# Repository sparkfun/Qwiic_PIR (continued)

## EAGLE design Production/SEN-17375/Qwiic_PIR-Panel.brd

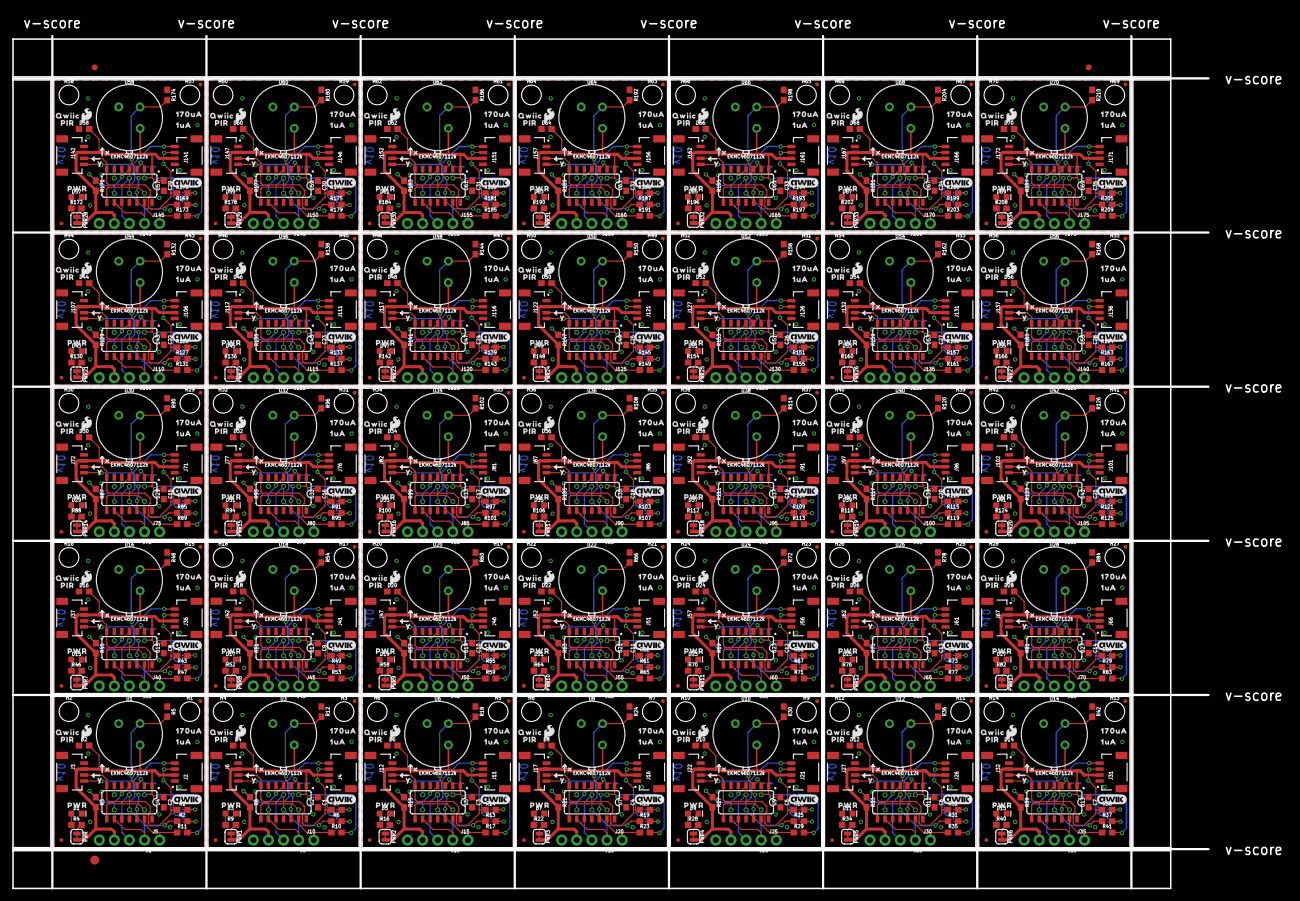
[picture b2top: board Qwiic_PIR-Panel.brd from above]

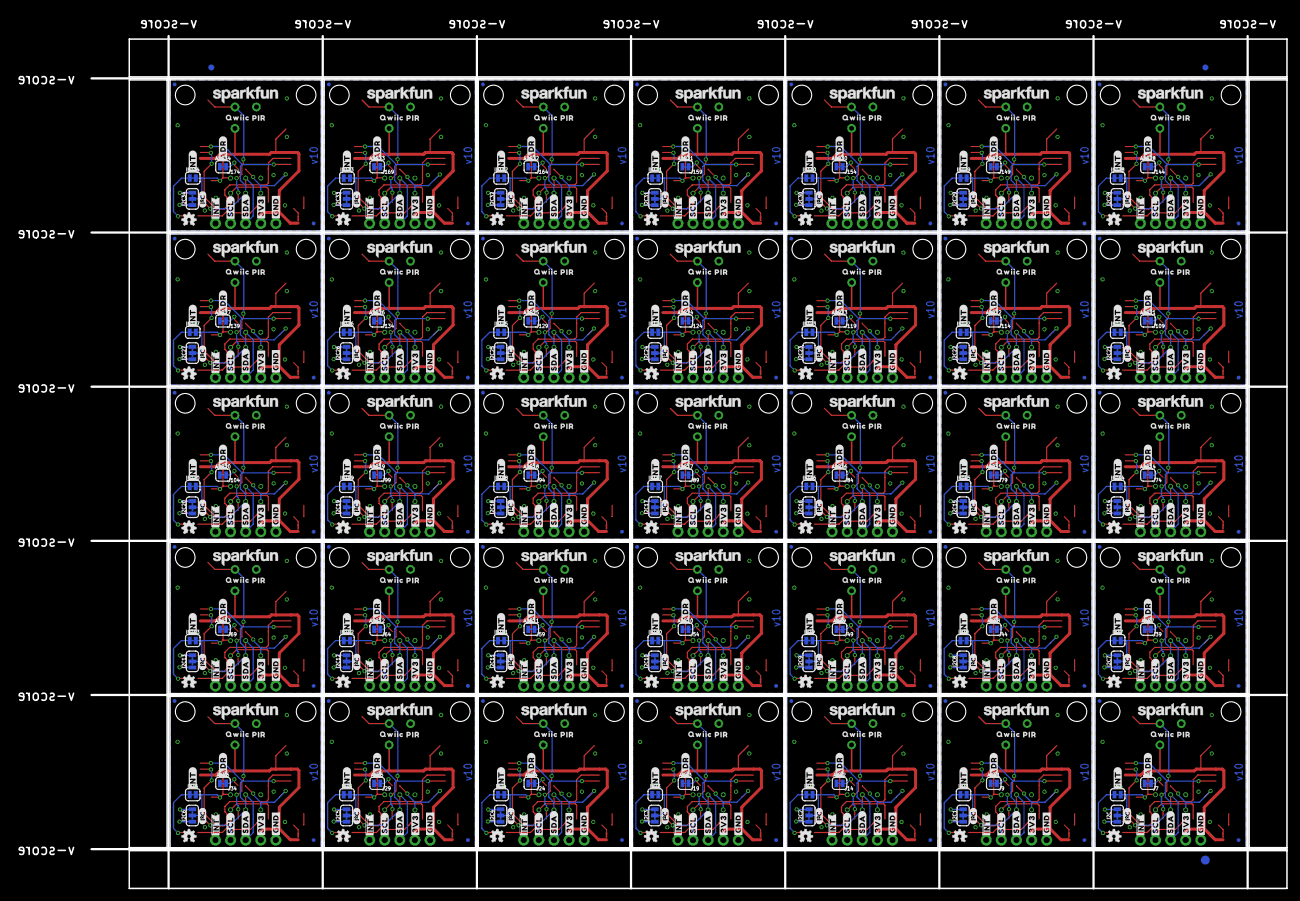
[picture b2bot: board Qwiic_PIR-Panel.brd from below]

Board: 2 copper layers, 214.1 x 147.1 mm, 1651 parts (633 on the bottom side), 490 nets.

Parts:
ADR, ADR1, ADR2, ADR3, ADR4, ADR5, ADR6, ADR7, ADR8, ADR9, ADR10, ADR11, ADR12, ADR13, ADR14, ADR15, ADR16, ADR17, ADR18, ADR19, ADR20, ADR21, ADR22, ADR23, ADR24, ADR25, ADR26, ADR27, ADR28, ADR29, ADR30, ADR31, ADR32, ADR33, ADR34: JUMPER-SMT_2_NC_TRACE_SILK; SMT-JUMPER_2_NC_TRACE_SILK
C1, C2, C3, C4, C5, C6, C7, C8, C9, C10, C11, C12, C13, C14, C15, C16, C17, C18, C19, C20, C21, C22, C23, C24, C25, C26, C27, C28, C29, C30, C31, C32, C33, C34, C35: 0.1uF; 0603
D1, D3, D5, D7, D9, D11, D13, D15, D17, D19, D21, D23, D25, D27, D29, D31, D33, D35, D37, D39, D41, D43, D45, D47, D49, D51, D53, D55, D57, D59, D61, D63, D65, D67, D69: RED; LED-0603
D2, D4, D6, D8, D10, D12, D14, D16, D18, D20, D22, D24, D26, D28, D30, D32, D34, D36, D38, D40, D42, D44, D46, D48, D50, D52, D54, D56, D58, D60, D62, D64, D66, D68, D70: 24V; 0603
E$1, E$2, E$3, E$4: FIDUCIAL-1X2
E$5, E$6: FIDUCIAL-1.5X3
H1, H2, H3, H4, H5, H6, H7, H8, H9, H10, H11, H12, H13, H14, H15, H16, H17, H18, H19, H20, H21, H22, H23, H24, H25, H26, H27, H28, H29, H30, H31, H32, H33, H34, H35, H36, H37, H38, H39, H40, H41, H42, H43, H44, H45, H46, H47, H48, H49, H50, H51, H52, H53, H54, H55, H56, H57, H58, H59, H60, H61, H62, H63, H64, H65, H66, H67, H68, H69, H70: STAND-OFF
I2C, I2C1, I2C2, I2C3, I2C4, I2C5, I2C6, I2C7, I2C8, I2C9, I2C10, I2C11, I2C12, I2C13, I2C14, I2C15, I2C16, I2C17, I2C18, I2C19, I2C20, I2C21, I2C22, I2C23, I2C24, I2C25, I2C26, I2C27, I2C28, I2C29, I2C30, I2C31, I2C32, I2C33, I2C34: JUMPER-SMT_3_2-NC_TRACE_SILK; SMT-JUMPER_3_2-NC_TRACE_SILK
INT, INT1, INT2, INT3, INT4, INT5, INT6, INT7, INT8, INT9, INT10, INT11, INT12, INT13, INT14, INT15, INT16, INT17, INT18, INT19, INT20, INT21, INT22, INT23, INT24, INT25, INT26, INT27, INT28, INT29, INT30, INT31, INT32, INT33, INT34: JUMPER-SMT_2_NC_TRACE_SILK; SMT-JUMPER_2_NC_TRACE_SILK
J1, J8, J13, J18, J23, J28, J33, J38, J43, J48, J53, J58, J63, J68, J73, J78, J83, J88, J93, J98, J103, J108, J113, J118, J123, J128, J133, J138, J143, J148, J153, J158, J163, J168, J173: 1X04_NO_SILK
J2, J3, J4, J6, J11, J12, J16, J17, J21, J22, J26, J27, J31, J32, J36, J37, J41, J42, J46, J47, J51, J52, J56, J57, J61, J62, J66, J67, J71, J72, J76, J77, J81, J82, J86, J87, J91, J92, J96, J97, J101, J102, J106, J107, J111, J112, J116, J117, J121, J122, J126, J127, J131, J132, J136, J137, J141, J142, J146, J147, J151, J152, J156, J157, J161, J162, J166, J167, J171, J172: QWIIC; JST04_1MM_RA
J5, J10, J15, J20, J25, J30, J35, J40, J45, J50, J55, J60, J65, J70, J75, J80, J85, J90, J95, J100, J105, J110, J115, J120, J125, J130, J135, J140, J145, J150, J155, J160, J165, J170, J175: 1X01_NO_SILK
J7, J9, J14, J19, J24, J29, J34, J39, J44, J49, J54, J59, J64, J69, J74, J79, J84, J89, J94, J99, J104, J109, J114, J119, J124, J129, J134, J139, J144, J149, J154, J159, J164, J169, J174: ISP; 2X3_TEST_POINTS
JP1, JP2, JP3, JP4, JP5, JP6, JP7, JP8, JP9, JP10, JP11, JP12, JP13, JP14, JP15, JP16, JP17, JP18, JP19, JP20, JP21, JP22, JP23, JP24, JP25, JP26, JP27, JP28, JP29, JP30, JP31, JP32, JP33, JP34, JP35, JP36, JP37, JP38, JP39, JP40, JP41, JP42, JP43, JP44, JP45, JP46, JP47, JP48, JP49, JP50, JP51, JP52, JP53, JP54, JP55, JP56, JP57, JP58, JP59, JP60, JP61, JP62, JP63, JP64, JP65, JP66, JP67, JP68, JP69, JP70, JP71, JP72, JP73, JP74, JP75, JP76, JP77, JP78, JP79, JP80, JP81, JP82, JP83, JP84, JP85, JP86, JP87, JP88, JP89, JP90, JP91, JP92, JP93, JP94, JP95, JP96, JP97, JP98, JP99, JP100, JP101, JP102, JP103, JP104, JP105, JP106, JP107, JP108, JP109, JP110, JP111, JP112, JP113, JP114, JP115, JP116, JP117, JP118, JP119, JP120, JP121, JP122, JP123, JP124, JP125, JP126, JP127, JP128, JP129, JP130, JP131, JP132, JP133, JP134, JP135, JP136, JP137, JP138, JP139, JP140: FIDUCIALUFIDUCIAL; MICRO-FIDUCIAL
LOGO1, LOGO5, LOGO9, LOGO13, LOGO17, LOGO21, LOGO25, LOGO29, LOGO33, LOGO37, LOGO41, LOGO45, LOGO49, LOGO53, LOGO57, LOGO61, LOGO65, LOGO69, LOGO73, LOGO77, LOGO81, LOGO85, LOGO89, LOGO93, LOGO97, LOGO101, LOGO105, LOGO109, LOGO113, LOGO117, LOGO121, LOGO125, LOGO129, LOGO133, LOGO137: OSHW-LOGOMINI; OSHW-LOGO-MINI
LOGO2, LOGO8, LOGO12, LOGO16, LOGO20, LOGO24, LOGO28, LOGO32, LOGO36, LOGO40, LOGO44, LOGO48, LOGO52, LOGO56, LOGO60, LOGO64, LOGO68, LOGO72, LOGO76, LOGO80, LOGO84, LOGO88, LOGO92, LOGO96, LOGO100, LOGO104, LOGO108, LOGO112, LOGO116, LOGO120, LOGO124, LOGO128, LOGO132, LOGO136, LOGO140: QWIIC_LOGO_5MM; QWIIC_5MM
LOGO3, LOGO6, LOGO10, LOGO14, LOGO18, LOGO22, LOGO26, LOGO30, LOGO34, LOGO38, LOGO42, LOGO46, LOGO50, LOGO54, LOGO58, LOGO62, LOGO66, LOGO70, LOGO74, LOGO78, LOGO82, LOGO86, LOGO90, LOGO94, LOGO98, LOGO102, LOGO106, LOGO110, LOGO114, LOGO118, LOGO122, LOGO126, LOGO130, LOGO134, LOGO138: SFE_LOGO_NAME.1_INCH; SFE_LOGO_NAME_.1
LOGO4, LOGO7, LOGO11, LOGO15, LOGO19, LOGO23, LOGO27, LOGO31, LOGO35, LOGO39, LOGO43, LOGO47, LOGO51, LOGO55, LOGO59, LOGO63, LOGO67, LOGO71, LOGO75, LOGO79, LOGO83, LOGO87, LOGO91, LOGO95, LOGO99, LOGO103, LOGO107, LOGO111, LOGO115, LOGO119, LOGO123, LOGO127, LOGO131, LOGO135, LOGO139: SFE_LOGO_FLAME.1_INCH; SFE_LOGO_FLAME_.1
PWR, PWR1, PWR2, PWR3, PWR4, PWR5, PWR6, PWR7, PWR8, PWR9, PWR10, PWR11, PWR12, PWR13, PWR14, PWR15, PWR16, PWR17, PWR18, PWR19, PWR20, PWR21, PWR22, PWR23, PWR24, PWR25, PWR26, PWR27, PWR28, PWR29, PWR30, PWR31, PWR32, PWR33, PWR34: JUMPER-SMT_2_NC_TRACE_SILK; SMT-JUMPER_2_NC_TRACE_SILK
R1, R2, R6, R7, R13, R14, R19, R20, R25, R26, R31, R32, R37, R38, R43, R44, R49, R50, R55, R56, R61, R62, R67, R68, R73, R74, R79, R80, R85, R86, R91, R92, R97, R98, R103, R104, R109, R110, R115, R116, R121, R122, R127, R128, R133, R134, R139, R140, R145, R146, R151, R152, R157, R158, R163, R164, R169, R170, R175, R176, R181, R182, R187, R188, R193, R194, R199, R200, R205, R206: 2.2k; 0603
R3, R8, R10, R11, R15, R17, R21, R23, R27, R29, R33, R35, R39, R41, R45, R47, R51, R53, R57, R59, R63, R65, R69, R71, R75, R77, R81, R83, R87, R89, R93, R95, R99, R101, R105, R107, R111, R113, R117, R119, R123, R125, R129, R131, R135, R137, R141, R143, R147, R149, R153, R155, R159, R161, R165, R167, R171, R173, R177, R179, R183, R185, R189, R191, R195, R197, R201, R203, R207, R209: 10k; 0603
R4, R9, R16, R22, R28, R34, R40, R46, R52, R58, R64, R70, R76, R82, R88, R94, R100, R106, R112, R118, R124, R130, R136, R142, R148, R154, R160, R166, R172, R178, R184, R190, R196, R202, R208: 1k; 0603
R5, R12, R18, R24, R30, R36, R42, R48, R54, R60, R66, R72, R78, R84, R90, R96, R102, R108, R114, R120, R126, R132, R138, R144, R150, R156, R162, R168, R174, R180, R186, R192, R198, R204, R210: 47k; 0603
U1, U3, U6, U8, U10, U12, U14, U16, U18, U20, U22, U24, U26, U28, U30, U32, U34, U36, U38, U40, U42, U44, U46, U48, U50, U52, U54, U56, U58, U60, U62, U64, U66, U68, U70: EKMC4607112k; TO-3
U2, U4, U5, U7, U9, U11, U13, U15, U17, U19, U21, U23, U25, U27, U29, U31, U33, U35, U37, U39, U41, U43, U45, U47, U49, U51, U53, U55, U57, U59, U61, U63, U65, U67, U69: ATTINY84-ARDUINO; SO14
U$1, U$13, U$15, U$23, U$36, U$40, U$53, U$57, U$70, U$74, U$87, U$91, U$104, U$108, U$121, U$125, U$138, U$142, U$155, U$159, U$172, U$176, U$189, U$193, U$206, U$210, U$223, U$227, U$240, U$244, U$257, U$261, U$274, U$278, U$291, U$295, U$308, U$312, U$325, U$329, U$342, U$346, U$359, U$363, U$376, U$380, U$393, U$397, U$410, U$414, U$427, U$431, U$444, U$448, U$461, U$465, U$478, U$482, U$495, U$499, U$512, U$516, U$529, U$533, U$546, U$550, U$563, U$567, U$580, U$584: PIR0
U$2, U$24, U$41, U$58, U$75, U$92, U$109, U$126, U$143, U$160, U$177, U$194, U$211, U$228, U$245, U$262, U$279, U$296, U$313, U$330, U$347, U$364, U$381, U$398, U$415, U$432, U$449, U$466, U$483, U$500, U$517, U$534, U$551, U$568, U$585: 170UA0
U$3, U$20, U$37, U$54, U$71, U$88, U$105, U$122, U$139, U$156, U$173, U$190, U$207, U$224, U$241, U$258, U$275, U$292, U$309, U$326, U$343, U$360, U$377, U$394, U$411, U$428, U$445, U$462, U$479, U$496, U$513, U$530, U$547, U$564, U$581: PWR0
U$4, U$21, U$38, U$55, U$72, U$89, U$106, U$123, U$140, U$157, U$174, U$191, U$208, U$225, U$242, U$259, U$276, U$293, U$310, U$327, U$344, U$361, U$378, U$395, U$412, U$429, U$446, U$463, U$480, U$497, U$514, U$531, U$548, U$565, U$582: #INT#0
U$5, U$31, U$48, U$65, U$82, U$99, U$116, U$133, U$150, U$167, U$184, U$201, U$218, U$235, U$252, U$269, U$286, U$303, U$320, U$337, U$354, U$371, U$388, U$405, U$422, U$439, U$456, U$473, U$490, U$507, U$524, U$541, U$558, U$575, U$592: #3V3#0
U$6, U$32, U$49, U$66, U$83, U$100, U$117, U$134, U$151, U$168, U$185, U$202, U$219, U$236, U$253, U$270, U$287, U$304, U$321, U$338, U$355, U$372, U$389, U$406, U$423, U$440, U$457, U$474, U$491, U$508, U$525, U$542, U$559, U$576, U$593: #SDA#0
U$7, U$33, U$50, U$67, U$84, U$101, U$118, U$135, U$152, U$169, U$186, U$203, U$220, U$237, U$254, U$271, U$288, U$305, U$322, U$339, U$356, U$373, U$390, U$407, U$424, U$441, U$458, U$475, U$492, U$509, U$526, U$543, U$560, U$577, U$594: #SCL#0
U$8, U$34, U$51, U$68, U$85, U$102, U$119, U$136, U$153, U$170, U$187, U$204, U$221, U$238, U$255, U$272, U$289, U$306, U$323, U$340, U$357, U$374, U$391, U$408, U$425, U$442, U$459, U$476, U$493, U$510, U$527, U$544, U$561, U$578, U$595: ##INT##0
U$9, U$25, U$42, U$59, U$76, U$93, U$110, U$127, U$144, U$161, U$178, U$195, U$212, U$229, U$246, U$263, U$280, U$297, U$314, U$331, U$348, U$365, U$382, U$399, U$416, U$433, U$450, U$467, U$484, U$501, U$518, U$535, U$552, U$569, U$586: 1UA0
U$10, U$12, U$35, U$52, U$69, U$86, U$103, U$120, U$137, U$154, U$171, U$188, U$205, U$222, U$239, U$256, U$273, U$290, U$307, U$324, U$341, U$358, U$375, U$392, U$409, U$426, U$443, U$460, U$477, U$494, U$511, U$528, U$545, U$562, U$579: I_SUPER2_C-()-03
U$11, U$22, U$39, U$56, U$73, U$90, U$107, U$124, U$141, U$158, U$175, U$192, U$209, U$226, U$243, U$260, U$277, U$294, U$311, U$328, U$345, U$362, U$379, U$396, U$413, U$430, U$447, U$464, U$481, U$498, U$515, U$532, U$549, U$566, U$583: #ADR#0
U$14, U$26, U$43, U$60, U$77, U$94, U$111, U$128, U$145, U$162, U$179, U$196, U$213, U$230, U$247, U$264, U$281, U$298, U$315, U$332, U$349, U$366, U$383, U$400, U$417, U$434, U$451, U$468, U$485, U$502, U$519, U$536, U$553, U$570, U$587: X0
U$16, U$27, U$44, U$61, U$78, U$95, U$112, U$129, U$146, U$163, U$180, U$197, U$214, U$231, U$248, U$265, U$282, U$299, U$316, U$333, U$350, U$367, U$384, U$401, U$418, U$435, U$452, U$469, U$486, U$503, U$520, U$537, U$554, U$571, U$588: Y0
U$17, U$18, U$28, U$29, U$45, U$46, U$62, U$63, U$79, U$80, U$96, U$97, U$113, U$114, U$130, U$131, U$147, U$148, U$164, U$165, U$181, U$182, U$198, U$199, U$215, U$216, U$232, U$233, U$249, U$250, U$266, U$267, U$283, U$284, U$300, U$301, U$317, U$318, U$334, U$335, U$351, U$352, U$368, U$369, U$385, U$386, U$402, U$403, U$419, U$420, U$436, U$437, U$453, U$454, U$470, U$471, U$487, U$488, U$504, U$505, U$521, U$522, U$538, U$539, U$555, U$556, U$572, U$573, U$589, U$590: QWIIC0
U$19, U$30, U$47, U$64, U$81, U$98, U$115, U$132, U$149, U$166, U$183, U$200, U$217, U$234, U$251, U$268, U$285, U$302, U$319, U$336, U$353, U$370, U$387, U$404, U$421, U$438, U$455, U$472, U$489, U$506, U$523, U$540, U$557, U$574, U$591: #GND#0

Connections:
3.3V: C2.1, D2.2, I2C.2, INT.2, J1.3, J2.2, J3.2, J7.2, PWR.2, R3.2, U1.VDD, U4.1
3.3V1: C1.1, D4.2, I2C1.2, INT1.2, J4.2, J6.2, J8.3, J9.2, PWR1.2, R8.2, U2.1, U3.VDD
3.3V2: C3.1, D6.2, I2C2.2, INT2.2, J11.2, J12.2, J13.3, J14.2, PWR2.2, R15.2, U5.1, U6.VDD
3.3V3: C4.1, D8.2, I2C3.2, INT3.2, J16.2, J17.2, J18.3, J19.2, PWR3.2, R21.2, U7.1, U8.VDD
3.3V4: C5.1, D10.2, I2C4.2, INT4.2, J21.2, J22.2, J23.3, J24.2, PWR4.2, R27.2, U9.1, U10.VDD
3.3V5: C6.1, D12.2, I2C5.2, INT5.2, J26.2, J27.2, J28.3, J29.2, PWR5.2, R33.2, U11.1, U12.VDD
3.3V6: C7.1, D14.2, I2C6.2, INT6.2, J31.2, J32.2, J33.3, J34.2, PWR6.2, R39.2, U13.1, U14.VDD
3.3V7: C8.1, D16.2, I2C7.2, INT7.2, J36.2, J37.2, J38.3, J39.2, PWR7.2, R45.2, U15.1, U16.VDD
3.3V8: C9.1, D18.2, I2C8.2, INT8.2, J41.2, J42.2, J43.3, J44.2, PWR8.2, R51.2, U17.1, U18.VDD
3.3V9: C10.1, D20.2, I2C9.2, INT9.2, J46.2, J47.2, J48.3, J49.2, PWR9.2, R57.2, U19.1, U20.VDD
3.3V10: C11.1, D22.2, I2C10.2, INT10.2, J51.2, J52.2, J53.3, J54.2, PWR10.2, R63.2, U21.1, U22.VDD
3.3V11: C12.1, D24.2, I2C11.2, INT11.2, J56.2, J57.2, J58.3, J59.2, PWR11.2, R69.2, U23.1, U24.VDD
3.3V12: C13.1, D26.2, I2C12.2, INT12.2, J61.2, J62.2, J63.3, J64.2, PWR12.2, R75.2, U25.1, U26.VDD
3.3V13: C14.1, D28.2, I2C13.2, INT13.2, J66.2, J67.2, J68.3, J69.2, PWR13.2, R81.2, U27.1, U28.VDD
3.3V14: C15.1, D30.2, I2C14.2, INT14.2, J71.2, J72.2, J73.3, J74.2, PWR14.2, R87.2, U29.1, U30.VDD
3.3V15: C16.1, D32.2, I2C15.2, INT15.2, J76.2, J77.2, J78.3, J79.2, PWR15.2, R93.2, U31.1, U32.VDD
3.3V16: C17.1, D34.2, I2C16.2, INT16.2, J81.2, J82.2, J83.3, J84.2, PWR16.2, R99.2, U33.1, U34.VDD
3.3V17: C18.1, D36.2, I2C17.2, INT17.2, J86.2, J87.2, J88.3, J89.2, PWR17.2, R105.2, U35.1, U36.VDD
3.3V18: C19.1, D38.2, I2C18.2, INT18.2, J91.2, J92.2, J93.3, J94.2, PWR18.2, R111.2, U37.1, U38.VDD
3.3V19: C20.1, D40.2, I2C19.2, INT19.2, J96.2, J97.2, J98.3, J99.2, PWR19.2, R117.2, U39.1, U40.VDD
3.3V20: C21.1, D42.2, I2C20.2, INT20.2, J101.2, J102.2, J103.3, J104.2, PWR20.2, R123.2, U41.1, U42.VDD
3.3V21: C22.1, D44.2, I2C21.2, INT21.2, J106.2, J107.2, J108.3, J109.2, PWR21.2, R129.2, U43.1, U44.VDD
3.3V22: C23.1, D46.2, I2C22.2, INT22.2, J111.2, J112.2, J113.3, J114.2, PWR22.2, R135.2, U45.1, U46.VDD
3.3V23: C24.1, D48.2, I2C23.2, INT23.2, J116.2, J117.2, J118.3, J119.2, PWR23.2, R141.2, U47.1, U48.VDD
3.3V24: C25.1, D50.2, I2C24.2, INT24.2, J121.2, J122.2, J123.3, J124.2, PWR24.2, R147.2, U49.1, U50.VDD
3.3V25: C26.1, D52.2, I2C25.2, INT25.2, J126.2, J127.2, J128.3, J129.2, PWR25.2, R153.2, U51.1, U52.VDD
3.3V26: C27.1, D54.2, I2C26.2, INT26.2, J131.2, J132.2, J133.3, J134.2, PWR26.2, R159.2, U53.1, U54.VDD
3.3V27: C28.1, D56.2, I2C27.2, INT27.2, J136.2, J137.2, J138.3, J139.2, PWR27.2, R165.2, U55.1, U56.VDD
3.3V28: C29.1, D58.2, I2C28.2, INT28.2, J141.2, J142.2, J143.3, J144.2, PWR28.2, R171.2, U57.1, U58.VDD
3.3V29: C30.1, D60.2, I2C29.2, INT29.2, J146.2, J147.2, J148.3, J149.2, PWR29.2, R177.2, U59.1, U60.VDD
3.3V30: C31.1, D62.2, I2C30.2, INT30.2, J151.2, J152.2, J153.3, J154.2, PWR30.2, R183.2, U61.1, U62.VDD
3.3V31: C32.1, D64.2, I2C31.2, INT31.2, J156.2, J157.2, J158.3, J159.2, PWR31.2, R189.2, U63.1, U64.VDD
3.3V32: C33.1, D66.2, I2C32.2, INT32.2, J161.2, J162.2, J163.3, J164.2, PWR32.2, R195.2, U65.1, U66.VDD
3.3V33: C34.1, D68.2, I2C33.2, INT33.2, J166.2, J167.2, J168.3, J169.2, PWR33.2, R201.2, U67.1, U68.VDD
3.3V34: C35.1, D70.2, I2C34.2, INT34.2, J171.2, J172.2, J173.3, J174.2, PWR34.2, R207.2, U69.1, U70.VDD
!INT: J5.1, R11.1, U4.13
!INT1: J10.1, R10.1, U2.13
!INT2: J15.1, R17.1, U5.13
!INT3: J20.1, R23.1, U7.13
!INT4: J25.1, R29.1, U9.13
!INT5: J30.1, R35.1, U11.13
!INT6: J35.1, R41.1, U13.13
!INT7: J40.1, R47.1, U15.13
!INT8: J45.1, R53.1, U17.13
!INT9: J50.1, R59.1, U19.13
!INT10: J55.1, R65.1, U21.13
!INT11: J60.1, R71.1, U23.13
!INT12: J65.1, R77.1, U25.13
!INT13: J70.1, R83.1, U27.13
!INT14: J75.1, R89.1, U29.13
!INT15: J80.1, R95.1, U31.13
!INT16: J85.1, R101.1, U33.13
!INT17: J90.1, R107.1, U35.13
!INT18: J95.1, R113.1, U37.13
!INT19: J100.1, R119.1, U39.13
!INT20: J105.1, R125.1, U41.13
!INT21: J110.1, R131.1, U43.13
!INT22: J115.1, R137.1, U45.13
!INT23: J120.1, R143.1, U47.13
!INT24: J125.1, R149.1, U49.13
!INT25: J130.1, R155.1, U51.13
!INT26: J135.1, R161.1, U53.13
!INT27: J140.1, R167.1, U55.13
!INT28: J145.1, R173.1, U57.13
!INT29: J150.1, R179.1, U59.13
!INT30: J155.1, R185.1, U61.13
!INT31: J160.1, R191.1, U63.13
!INT32: J165.1, R197.1, U65.13
!INT33: J170.1, R203.1, U67.13
!INT34: J175.1, R209.1, U69.13
!RST: J7.5, R3.1, U4.4
!RST1: J9.5, R8.1, U2.4
!RST2: J14.5, R15.1, U5.4
!RST3: J19.5, R21.1, U7.4
!RST4: J24.5, R27.1, U9.4
!RST5: J29.5, R33.1, U11.4
!RST6: J34.5, R39.1, U13.4
!RST7: J39.5, R45.1, U15.4
!RST8: J44.5, R51.1, U17.4
!RST9: J49.5, R57.1, U19.4
!RST10: J54.5, R63.1, U21.4
!RST11: J59.5, R69.1, U23.4
!RST12: J64.5, R75.1, U25.4
!RST13: J69.5, R81.1, U27.4
!RST14: J74.5, R87.1, U29.4
!RST15: J79.5, R93.1, U31.4
!RST16: J84.5, R99.1, U33.4
!RST17: J89.5, R105.1, U35.4
!RST18: J94.5, R111.1, U37.4
!RST19: J99.5, R117.1, U39.4
!RST20: J104.5, R123.1, U41.4
!RST21: J109.5, R129.1, U43.4
!RST22: J114.5, R135.1, U45.4
!RST23: J119.5, R141.1, U47.4
!RST24: J124.5, R147.1, U49.4
!RST25: J129.5, R153.1, U51.4
!RST26: J134.5, R159.1, U53.4
!RST27: J139.5, R165.1, U55.4
!RST28: J144.5, R171.1, U57.4
!RST29: J149.5, R177.1, U59.4
!RST30: J154.5, R183.1, U61.4
!RST31: J159.5, R189.1, U63.4
!RST32: J164.5, R195.1, U65.4
!RST33: J169.5, R201.1, U67.4
!RST34: J174.5, R207.1, U69.4
ADR0: ADR.2, U4.3
ADR1: ADR1.2, U2.3
ADR2: ADR2.2, U5.3
ADR3: ADR3.2, U7.3
ADR4: ADR4.2, U9.3
ADR5: ADR5.2, U11.3
ADR6: ADR6.2, U13.3
ADR7: ADR7.2, U15.3
ADR8: ADR8.2, U17.3
ADR9: ADR9.2, U19.3
ADR10: ADR10.2, U21.3
ADR11: ADR11.2, U23.3
ADR12: ADR12.2, U25.3
ADR13: ADR13.2, U27.3
ADR14: ADR14.2, U29.3
ADR15: ADR15.2, U31.3
ADR16: ADR16.2, U33.3
ADR17: ADR17.2, U35.3
ADR18: ADR18.2, U37.3
ADR19: ADR19.2, U39.3
ADR20: ADR20.2, U41.3
ADR21: ADR21.2, U43.3
ADR22: ADR22.2, U45.3
ADR23: ADR23.2, U47.3
ADR24: ADR24.2, U49.3
ADR25: ADR25.2, U51.3
ADR26: ADR26.2, U53.3
ADR27: ADR27.2, U55.3
ADR28: ADR28.2, U57.3
ADR29: ADR29.2, U59.3
ADR30: ADR30.2, U61.3
ADR31: ADR31.2, U63.3
ADR32: ADR32.2, U65.3
ADR33: ADR33.2, U67.3
ADR34: ADR34.2, U69.3
GND: ADR.1, C2.2, D1.C, D2.1, J1.4, J2.1, J3.1, J7.6, R5.1, U1.GND, U4.14
GND1: ADR1.1, C1.2, D3.C, D4.1, J4.1, J6.1, J8.4, J9.6, R12.1, U2.14, U3.GND
GND2: ADR2.1, C3.2, D5.C, D6.1, J11.1, J12.1, J13.4, J14.6, R18.1, U5.14, U6.GND
GND3: ADR3.1, C4.2, D7.C, D8.1, J16.1, J17.1, J18.4, J19.6, R24.1, U7.14, U8.GND
GND4: ADR4.1, C5.2, D9.C, D10.1, J21.1, J22.1, J23.4, J24.6, R30.1, U9.14, U10.GND
GND5: ADR5.1, C6.2, D11.C, D12.1, J26.1, J27.1, J28.4, J29.6, R36.1, U11.14, U12.GND
GND6: ADR6.1, C7.2, D13.C, D14.1, J31.1, J32.1, J33.4, J34.6, R42.1, U13.14, U14.GND
GND7: ADR7.1, C8.2, D15.C, D16.1, J36.1, J37.1, J38.4, J39.6, R48.1, U15.14, U16.GND
GND8: ADR8.1, C9.2, D17.C, D18.1, J41.1, J42.1, J43.4, J44.6, R54.1, U17.14, U18.GND
GND9: ADR9.1, C10.2, D19.C, D20.1, J46.1, J47.1, J48.4, J49.6, R60.1, U19.14, U20.GND
GND10: ADR10.1, C11.2, D21.C, D22.1, J51.1, J52.1, J53.4, J54.6, R66.1, U21.14, U22.GND
GND11: ADR11.1, C12.2, D23.C, D24.1, J56.1, J57.1, J58.4, J59.6, R72.1, U23.14, U24.GND
GND12: ADR12.1, C13.2, D25.C, D26.1, J61.1, J62.1, J63.4, J64.6, R78.1, U25.14, U26.GND
GND13: ADR13.1, C14.2, D27.C, D28.1, J66.1, J67.1, J68.4, J69.6, R84.1, U27.14, U28.GND
GND14: ADR14.1, C15.2, D29.C, D30.1, J71.1, J72.1, J73.4, J74.6, R90.1, U29.14, U30.GND
GND15: ADR15.1, C16.2, D31.C, D32.1, J76.1, J77.1, J78.4, J79.6, R96.1, U31.14, U32.GND
GND16: ADR16.1, C17.2, D33.C, D34.1, J81.1, J82.1, J83.4, J84.6, R102.1, U33.14, U34.GND
GND17: ADR17.1, C18.2, D35.C, D36.1, J86.1, J87.1, J88.4, J89.6, R108.1, U35.14, U36.GND
GND18: ADR18.1, C19.2, D37.C, D38.1, J91.1, J92.1, J93.4, J94.6, R114.1, U37.14, U38.GND
GND19: ADR19.1, C20.2, D39.C, D40.1, J96.1, J97.1, J98.4, J99.6, R120.1, U39.14, U40.GND
GND20: ADR20.1, C21.2, D41.C, D42.1, J101.1, J102.1, J103.4, J104.6, R126.1, U41.14, U42.GND
GND21: ADR21.1, C22.2, D43.C, D44.1, J106.1, J107.1, J108.4, J109.6, R132.1, U43.14, U44.GND
GND22: ADR22.1, C23.2, D45.C, D46.1, J111.1, J112.1, J113.4, J114.6, R138.1, U45.14, U46.GND
GND23: ADR23.1, C24.2, D47.C, D48.1, J116.1, J117.1, J118.4, J119.6, R144.1, U47.14, U48.GND
GND24: ADR24.1, C25.2, D49.C, D50.1, J121.1, J122.1, J123.4, J124.6, R150.1, U49.14, U50.GND
GND25: ADR25.1, C26.2, D51.C, D52.1, J126.1, J127.1, J128.4, J129.6, R156.1, U51.14, U52.GND
GND26: ADR26.1, C27.2, D53.C, D54.1, J131.1, J132.1, J133.4, J134.6, R162.1, U53.14, U54.GND
GND27: ADR27.1, C28.2, D55.C, D56.1, J136.1, J137.1, J138.4, J139.6, R168.1, U55.14, U56.GND
GND28: ADR28.1, C29.2, D57.C, D58.1, J141.1, J142.1, J143.4, J144.6, R174.1, U57.14, U58.GND
GND29: ADR29.1, C30.2, D59.C, D60.1, J146.1, J147.1, J148.4, J149.6, R180.1, U59.14, U60.GND
GND30: ADR30.1, C31.2, D61.C, D62.1, J151.1, J152.1, J153.4, J154.6, R186.1, U61.14, U62.GND
GND31: ADR31.1, C32.2, D63.C, D64.1, J156.1, J157.1, J158.4, J159.6, R192.1, U63.14, U64.GND
GND32: ADR32.1, C33.2, D65.C, D66.1, J161.1, J162.1, J163.4, J164.6, R198.1, U65.14, U66.GND
GND33: ADR33.1, C34.2, D67.C, D68.1, J166.1, J167.1, J168.4, J169.6, R204.1, U67.14, U68.GND
GND34: ADR34.1, C35.2, D69.C, D70.1, J171.1, J172.1, J173.4, J174.6, R210.1, U69.14, U70.GND
INT_R: INT.1, R11.2
INT_R1: INT1.1, R10.2
INT_R2: INT2.1, R17.2
INT_R3: INT3.1, R23.2
INT_R4: INT4.1, R29.2
INT_R5: INT5.1, R35.2
INT_R6: INT6.1, R41.2
INT_R7: INT7.1, R47.2
INT_R8: INT8.1, R53.2
INT_R9: INT9.1, R59.2
INT_R10: INT10.1, R65.2
INT_R11: INT11.1, R71.2
INT_R12: INT12.1, R77.2
INT_R13: INT13.1, R83.2
INT_R14: INT14.1, R89.2
INT_R15: INT15.1, R95.2
INT_R16: INT16.1, R101.2
INT_R17: INT17.1, R107.2
INT_R18: INT18.1, R113.2
INT_R19: INT19.1, R119.2
INT_R20: INT20.1, R125.2
INT_R21: INT21.1, R131.2
INT_R22: INT22.1, R137.2
INT_R23: INT23.1, R143.2
INT_R24: INT24.1, R149.2
INT_R25: INT25.1, R155.2
INT_R26: INT26.1, R161.2
INT_R27: INT27.1, R167.2
INT_R28: INT28.1, R173.2
INT_R29: INT29.1, R179.2
INT_R30: INT30.1, R185.2
INT_R31: INT31.1, R191.2
INT_R32: INT32.1, R197.2
INT_R33: INT33.1, R203.2
INT_R34: INT34.1, R209.2
unnamed: D3.A, R9.1
unnamed: D5.A, R16.1
unnamed: D1.A, R4.1
unnamed: D7.A, R22.1
unnamed: D9.A, R28.1
unnamed: D11.A, R34.1
unnamed: D13.A, R40.1
unnamed: D15.A, R46.1
unnamed: D17.A, R52.1
unnamed: D19.A, R58.1
unnamed: D21.A, R64.1
unnamed: D23.A, R70.1
unnamed: D25.A, R76.1
unnamed: D27.A, R82.1
unnamed: D29.A, R88.1
unnamed: D31.A, R94.1
unnamed: D33.A, R100.1
unnamed: D35.A, R106.1
unnamed: D37.A, R112.1
unnamed: D39.A, R118.1
unnamed: D41.A, R124.1
unnamed: D43.A, R130.1
unnamed: D45.A, R136.1
unnamed: D47.A, R142.1
unnamed: D49.A, R148.1
unnamed: D51.A, R154.1
unnamed: D53.A, R160.1
unnamed: D55.A, R166.1
unnamed: D57.A, R172.1
unnamed: D59.A, R178.1
unnamed: D61.A, R184.1
unnamed: D63.A, R190.1
unnamed: D65.A, R196.1
unnamed: D67.A, R202.1
unnamed: D69.A, R208.1
PIR_OUT: R5.2, U1.OUT, U4.12
PIR_OUT1: R12.2, U2.12, U3.OUT
PIR_OUT2: R18.2, U5.12, U6.OUT
PIR_OUT3: R24.2, U7.12, U8.OUT
PIR_OUT4: R30.2, U9.12, U10.OUT
PIR_OUT5: R36.2, U11.12, U12.OUT
PIR_OUT6: R42.2, U13.12, U14.OUT
PIR_OUT7: R48.2, U15.12, U16.OUT
PIR_OUT8: R54.2, U17.12, U18.OUT
PIR_OUT9: R60.2, U19.12, U20.OUT
PIR_OUT10: R66.2, U21.12, U22.OUT
PIR_OUT11: R72.2, U23.12, U24.OUT
PIR_OUT12: R78.2, U25.12, U26.OUT
PIR_OUT13: R84.2, U27.12, U28.OUT
PIR_OUT14: R90.2, U29.12, U30.OUT
PIR_OUT15: R96.2, U31.12, U32.OUT
PIR_OUT16: R102.2, U33.12, U34.OUT
PIR_OUT17: R108.2, U35.12, U36.OUT
PIR_OUT18: R114.2, U37.12, U38.OUT
PIR_OUT19: R120.2, U39.12, U40.OUT
PIR_OUT20: R126.2, U41.12, U42.OUT
PIR_OUT21: R132.2, U43.12, U44.OUT
PIR_OUT22: R138.2, U45.12, U46.OUT
PIR_OUT23: R144.2, U47.12, U48.OUT
PIR_OUT24: R150.2, U49.12, U50.OUT
PIR_OUT25: R156.2, U51.12, U52.OUT
PIR_OUT26: R162.2, U53.12, U54.OUT
PIR_OUT27: R168.2, U55.12, U56.OUT
PIR_OUT28: R174.2, U57.12, U58.OUT
PIR_OUT29: R180.2, U59.12, U60.OUT
PIR_OUT30: R186.2, U61.12, U62.OUT
PIR_OUT31: R192.2, U63.12, U64.OUT
PIR_OUT32: R198.2, U65.12, U66.OUT
PIR_OUT33: R204.2, U67.12, U68.OUT
PIR_OUT34: R210.2, U69.12, U70.OUT
SCL: J1.1, J2.4, J3.4, J7.3, R2.1, U4.9
SCL1: J4.4, J6.4, J8.1, J9.3, R6.1, U2.9
SCL2: J11.4, J12.4, J13.1, J14.3, R13.1, U5.9
SCL3: J16.4, J17.4, J18.1, J19.3, R19.1, U7.9
SCL4: J21.4, J22.4, J23.1, J24.3, R25.1, U9.9
SCL5: J26.4, J27.4, J28.1, J29.3, R31.1, U11.9
SCL6: J31.4, J32.4, J33.1, J34.3, R37.1, U13.9
SCL7: J36.4, J37.4, J38.1, J39.3, R43.1, U15.9
SCL8: J41.4, J42.4, J43.1, J44.3, R49.1, U17.9
SCL9: J46.4, J47.4, J48.1, J49.3, R55.1, U19.9
SCL10: J51.4, J52.4, J53.1, J54.3, R61.1, U21.9
SCL11: J56.4, J57.4, J58.1, J59.3, R67.1, U23.9
SCL12: J61.4, J62.4, J63.1, J64.3, R73.1, U25.9
SCL13: J66.4, J67.4, J68.1, J69.3, R79.1, U27.9
SCL14: J71.4, J72.4, J73.1, J74.3, R85.1, U29.9
SCL15: J76.4, J77.4, J78.1, J79.3, R91.1, U31.9
SCL16: J81.4, J82.4, J83.1, J84.3, R97.1, U33.9
SCL17: J86.4, J87.4, J88.1, J89.3, R103.1, U35.9
SCL18: J91.4, J92.4, J93.1, J94.3, R109.1, U37.9
SCL19: J96.4, J97.4, J98.1, J99.3, R115.1, U39.9
SCL20: J101.4, J102.4, J103.1, J104.3, R121.1, U41.9
SCL21: J106.4, J107.4, J108.1, J109.3, R127.1, U43.9
SCL22: J111.4, J112.4, J113.1, J114.3, R133.1, U45.9
SCL23: J116.4, J117.4, J118.1, J119.3, R139.1, U47.9
SCL24: J121.4, J122.4, J123.1, J124.3, R145.1, U49.9
SCL25: J126.4, J127.4, J128.1, J129.3, R151.1, U51.9
SCL26: J131.4, J132.4, J133.1, J134.3, R157.1, U53.9
SCL27: J136.4, J137.4, J138.1, J139.3, R163.1, U55.9
SCL28: J141.4, J142.4, J143.1, J144.3, R169.1, U57.9
SCL29: J146.4, J147.4, J148.1, J149.3, R175.1, U59.9
SCL30: J151.4, J152.4, J153.1, J154.3, R181.1, U61.9
SCL31: J156.4, J157.4, J158.1, J159.3, R187.1, U63.9
SCL32: J161.4, J162.4, J163.1, J164.3, R193.1, U65.9
SCL33: J166.4, J167.4, J168.1, J169.3, R199.1, U67.9
SCL34: J171.4, J172.4, J173.1, J174.3, R205.1, U69.9
SCL_PU1: I2C.1, R2.2
SCL_PU2: I2C1.1, R6.2
SCL_PU3: I2C2.1, R13.2
SCL_PU4: I2C3.1, R19.2
SCL_PU5: I2C4.1, R25.2
SCL_PU6: I2C5.1, R31.2
SCL_PU7: I2C6.1, R37.2
SCL_PU8: I2C7.1, R43.2
SCL_PU9: I2C8.1, R49.2
SCL_PU10: I2C9.1, R55.2
SCL_PU11: I2C10.1, R61.2
SCL_PU12: I2C11.1, R67.2
SCL_PU13: I2C12.1, R73.2
SCL_PU14: I2C13.1, R79.2
SCL_PU15: I2C14.1, R85.2
SCL_PU16: I2C15.1, R91.2
SCL_PU17: I2C16.1, R97.2
SCL_PU18: I2C17.1, R103.2
SCL_PU19: I2C18.1, R109.2
SCL_PU20: I2C19.1, R115.2
SCL_PU21: I2C20.1, R121.2
SCL_PU22: I2C21.1, R127.2
SCL_PU23: I2C22.1, R133.2
SCL_PU24: I2C23.1, R139.2
SCL_PU25: I2C24.1, R145.2
SCL_PU26: I2C25.1, R151.2
SCL_PU27: I2C26.1, R157.2
SCL_PU28: I2C27.1, R163.2
SCL_PU29: I2C28.1, R169.2
SCL_PU30: I2C29.1, R175.2
SCL_PU31: I2C30.1, R181.2
SCL_PU32: I2C31.1, R187.2
SCL_PU33: I2C32.1, R193.2
SCL_PU34: I2C33.1, R199.2
SCL_PU35: I2C34.1, R205.2
SDA: J1.2, J2.3, J3.3, J7.4, R1.1, U4.7
SDA1: J4.3, J6.3, J8.2, J9.4, R7.1, U2.7
SDA2: J11.3, J12.3, J13.2, J14.4, R14.1, U5.7
SDA3: J16.3, J17.3, J18.2, J19.4, R20.1, U7.7
SDA4: J21.3, J22.3, J23.2, J24.4, R26.1, U9.7
SDA5: J26.3, J27.3, J28.2, J29.4, R32.1, U11.7
SDA6: J31.3, J32.3, J33.2, J34.4, R38.1, U13.7
SDA7: J36.3, J37.3, J38.2, J39.4, R44.1, U15.7
SDA8: J41.3, J42.3, J43.2, J44.4, R50.1, U17.7
SDA9: J46.3, J47.3, J48.2, J49.4, R56.1, U19.7
SDA10: J51.3, J52.3, J53.2, J54.4, R62.1, U21.7
SDA11: J56.3, J57.3, J58.2, J59.4, R68.1, U23.7
SDA12: J61.3, J62.3, J63.2, J64.4, R74.1, U25.7
SDA13: J66.3, J67.3, J68.2, J69.4, R80.1, U27.7
SDA14: J71.3, J72.3, J73.2, J74.4, R86.1, U29.7
SDA15: J76.3, J77.3, J78.2, J79.4, R92.1, U31.7
SDA16: J81.3, J82.3, J83.2, J84.4, R98.1, U33.7
SDA17: J86.3, J87.3, J88.2, J89.4, R104.1, U35.7
SDA18: J91.3, J92.3, J93.2, J94.4, R110.1, U37.7
SDA19: J96.3, J97.3, J98.2, J99.4, R116.1, U39.7
SDA20: J101.3, J102.3, J103.2, J104.4, R122.1, U41.7
SDA21: J106.3, J107.3, J108.2, J109.4, R128.1, U43.7
SDA22: J111.3, J112.3, J113.2, J114.4, R134.1, U45.7
SDA23: J116.3, J117.3, J118.2, J119.4, R140.1, U47.7
SDA24: J121.3, J122.3, J123.2, J124.4, R146.1, U49.7
SDA25: J126.3, J127.3, J128.2, J129.4, R152.1, U51.7
SDA26: J131.3, J132.3, J133.2, J134.4, R158.1, U53.7
SDA27: J136.3, J137.3, J138.2, J139.4, R164.1, U55.7
SDA28: J141.3, J142.3, J143.2, J144.4, R170.1, U57.7
SDA29: J146.3, J147.3, J148.2, J149.4, R176.1, U59.7
SDA30: J151.3, J152.3, J153.2, J154.4, R182.1, U61.7
SDA31: J156.3, J157.3, J158.2, J159.4, R188.1, U63.7
SDA32: J161.3, J162.3, J163.2, J164.4, R194.1, U65.7
SDA33: J166.3, J167.3, J168.2, J169.4, R200.1, U67.7
SDA34: J171.3, J172.3, J173.2, J174.4, R206.1, U69.7
SDA_PU1: I2C.3, R1.2
SDA_PU2: I2C1.3, R7.2
SDA_PU3: I2C2.3, R14.2
SDA_PU4: I2C3.3, R20.2
SDA_PU5: I2C4.3, R26.2
SDA_PU6: I2C5.3, R32.2
SDA_PU7: I2C6.3, R38.2
SDA_PU8: I2C7.3, R44.2
SDA_PU9: I2C8.3, R50.2
SDA_PU10: I2C9.3, R56.2
SDA_PU11: I2C10.3, R62.2
SDA_PU12: I2C11.3, R68.2
SDA_PU13: I2C12.3, R74.2
SDA_PU14: I2C13.3, R80.2
SDA_PU15: I2C14.3, R86.2
SDA_PU16: I2C15.3, R92.2
SDA_PU17: I2C16.3, R98.2
SDA_PU18: I2C17.3, R104.2
SDA_PU19: I2C18.3, R110.2
SDA_PU20: I2C19.3, R116.2
SDA_PU21: I2C20.3, R122.2
SDA_PU22: I2C21.3, R128.2
SDA_PU23: I2C22.3, R134.2
SDA_PU24: I2C23.3, R140.2
SDA_PU25: I2C24.3, R146.2
SDA_PU26: I2C25.3, R152.2
SDA_PU27: I2C26.3, R158.2
SDA_PU28: I2C27.3, R164.2
SDA_PU29: I2C28.3, R170.2
SDA_PU30: I2C29.3, R176.2
SDA_PU31: I2C30.3, R182.2
SDA_PU32: I2C31.3, R188.2
SDA_PU33: I2C32.3, R194.2
SDA_PU34: I2C33.3, R200.2
SDA_PU35: I2C34.3, R206.2
SDO: J7.1, U4.8
SDO1: J9.1, U2.8
SDO2: J14.1, U5.8
SDO3: J19.1, U7.8
SDO4: J24.1, U9.8
SDO5: J29.1, U11.8
SDO6: J34.1, U13.8
SDO7: J39.1, U15.8
SDO8: J44.1, U17.8
SDO9: J49.1, U19.8
SDO10: J54.1, U21.8
SDO11: J59.1, U23.8
SDO12: J64.1, U25.8
SDO13: J69.1, U27.8
SDO14: J74.1, U29.8
SDO15: J79.1, U31.8
SDO16: J84.1, U33.8
SDO17: J89.1, U35.8
SDO18: J94.1, U37.8
SDO19: J99.1, U39.8
SDO20: J104.1, U41.8
SDO21: J109.1, U43.8
SDO22: J114.1, U45.8
SDO23: J119.1, U47.8
SDO24: J124.1, U49.8
SDO25: J129.1, U51.8
SDO26: J134.1, U53.8
SDO27: J139.1, U55.8
SDO28: J144.1, U57.8
SDO29: J149.1, U59.8
SDO30: J154.1, U61.8
SDO31: J159.1, U63.8
SDO32: J164.1, U65.8
SDO33: J169.1, U67.8
SDO34: J174.1, U69.8
STAT: PWR.1, R4.2
STAT1: PWR1.1, R9.2
STAT2: PWR2.1, R16.2
STAT3: PWR3.1, R22.2
STAT4: PWR4.1, R28.2
STAT5: PWR5.1, R34.2
STAT6: PWR6.1, R40.2
STAT7: PWR7.1, R46.2
STAT8: PWR8.1, R52.2
STAT9: PWR9.1, R58.2
STAT10: PWR10.1, R64.2
STAT11: PWR11.1, R70.2
STAT12: PWR12.1, R76.2
STAT13: PWR13.1, R82.2
STAT14: PWR14.1, R88.2
STAT15: PWR15.1, R94.2
STAT16: PWR16.1, R100.2
STAT17: PWR17.1, R106.2
STAT18: PWR18.1, R112.2
STAT19: PWR19.1, R118.2
STAT20: PWR20.1, R124.2
STAT21: PWR21.1, R130.2
STAT22: PWR22.1, R136.2
STAT23: PWR23.1, R142.2
STAT24: PWR24.1, R148.2
STAT25: PWR25.1, R154.2
STAT26: PWR26.1, R160.2
STAT27: PWR27.1, R166.2
STAT28: PWR28.1, R172.2
STAT29: PWR29.1, R178.2
STAT30: PWR30.1, R184.2
STAT31: PWR31.1, R190.2
STAT32: PWR32.1, R196.2
STAT33: PWR33.1, R202.2
STAT34: PWR34.1, R208.2

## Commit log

2020-10-07 post checklist changes
2020-10-09 Panelizing
2020-10-12 adding fiducial to panel
2020-10-12 moving production folder
2020-10-12 changing panel to remove manually added fiducial
2020-10-21 adding panel for 1uA
2021-01-18 push for computer migration
2021-01-27 Update README.md
    Updating README from template copy.
2021-02-05 updating interrupts in firmware to single event triggered interrupt
2021-03-08 adding popQueue fix
2021-03-09 commenting out line 228
2021-03-23 Re-exported binaries
    Updated comments in Qwiic_PIR, queue.h, and registers.h
